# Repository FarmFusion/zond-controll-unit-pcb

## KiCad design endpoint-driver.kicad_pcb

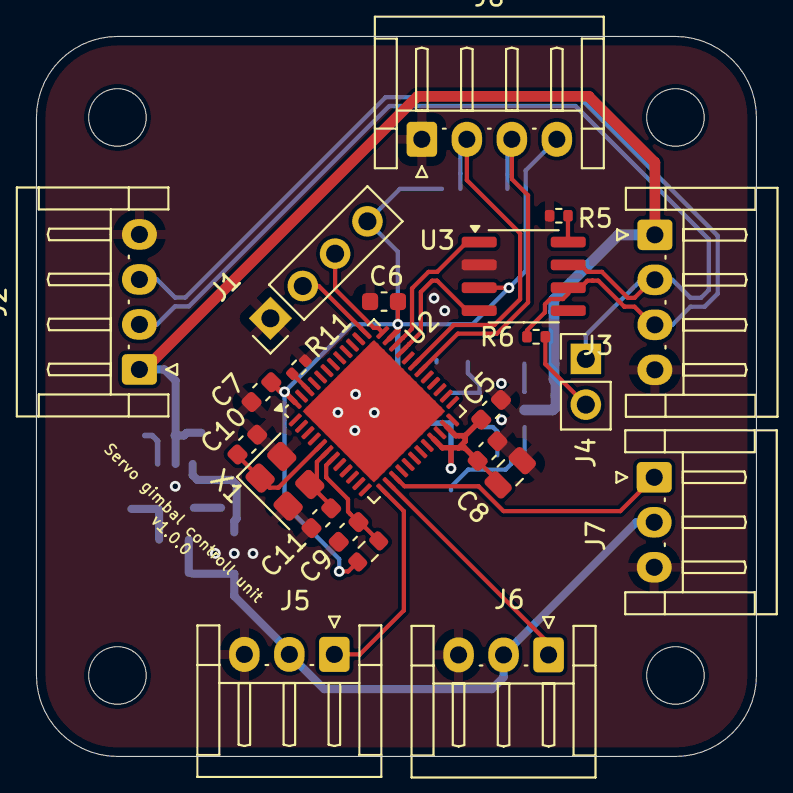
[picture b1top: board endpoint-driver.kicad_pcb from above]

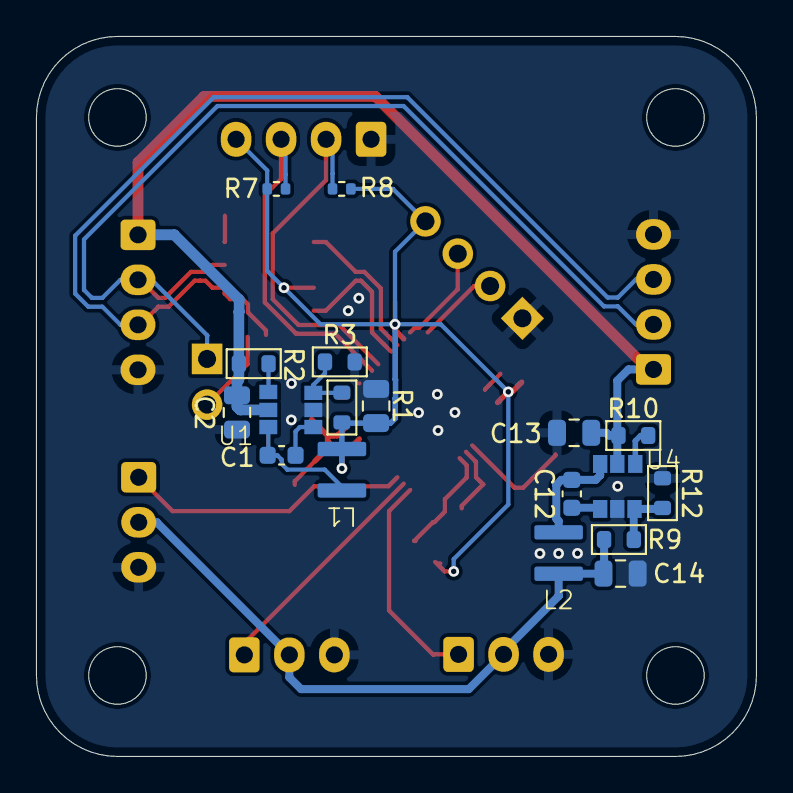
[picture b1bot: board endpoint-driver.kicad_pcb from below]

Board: 2 copper layers, 40.0 x 40.0 mm, 45 parts (18 on the bottom side), 29 nets.

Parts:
C1, C4, C5, C6, C7, C9, C12: 100nF; C_0603_1608Metric
C2, C13: 4.7uF; C_0805_2012Metric
C3, C8, C14: 10uF; C_0805_2012Metric
C10, C11: 20pF; C_0603_1608Metric
H1, H2, H3, H4: MountingHole_M3; MountingHole_3.2mm_M3
J1: Conn_01x04; PinHeader_1x04_P2.54mm_Vertical
J2, J3: Conn_01x04_Pin; JST_EH_S4B-EH_1x04_P2.50mm_Horizontal
J4: Conn_01x02_Pin; PinHeader_1x02_P2.54mm_Vertical
J5, J6, J7: Conn_01x03_Pin; JST_EH_S3B-EH_1x03_P2.50mm_Horizontal
J8: Conn_01x04; JST_EH_S4B-EH_1x04_P2.50mm_Horizontal
L1, L2: 4.7uH; SNR3015K-4R7M
R1, R9: 16kOm; R_0603_1608Metric
R2, R4, R10: 100kOm; R_0603_1608Metric
R3: 5.1kOm; R_0603_1608Metric
R5, R6, R7, R8, R11: 10kOm; R_0402_1005Metric
R12: 3kOm; R_0603_1608Metric
U1, U4: JW5017S
U2: STM32G431CBUx; QFN-48-1EP_7x7mm_P0.5mm_EP5.6x5.6mm
U3: SN65HVD230; SOIC-8_3.9x4.9mm_P1.27mm
X1: Crystal_Generic; Crystal_SMD_3225-4Pin_3.2x2.5mm

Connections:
+3.3V: C3.1, C4.1, C5.1, C6.1, C7.1, C8.1, J1.4, J8.4, L1.1, R1.1, R4.1, R7.1, R8.1, U2.21 (VDDA), U2.23 (VDD), U2.35 (VDD), U2.48 (VDD), U3.3 (VCC)
+5V: C14.1, J5.2, J6.2, J7.2, L2.1, R9.1
/CAN/CAN_N: J2.3, J3.3, R6.2, U3.6 (CANL)
/CAN/CAN_OUT+: U2.34 (PA12), U3.1 (D)
/CAN/CAN_OUT-: U2.33 (PA11), U3.4 (R)
/CAN/CAN_P: J2.2, J3.2, J4.1, U3.7 (CANH)
/MCU/BOOT: R11.1, U2.46 (PB8)
/MCU/EXTI_BTN1: J5.1, U2.13 (PA5)
/MCU/EXTI_BTN2: J6.1, U2.14 (PA6)
/MCU/EXTI_BTN3: J7.1, U2.15 (PA7)
/MCU/NRST: C9.1, R4.2, U2.7 (PG10)
/MCU/OSC_IN: C10.1, U2.5 (PF0), X1.1
/MCU/OSC_OUT: C11.2, U2.6 (PF1), X1.3
/MCU/SCL: J8.2, R8.2, U2.31 (PA9)
/MCU/SDA: J8.3, R7.2, U2.30 (PA8)
/MCU/SWCLK: J1.2, U2.37 (PA14)
/MCU/SWDIO: J1.3, U2.36 (PA13)
GND: C2.2, C3.2, C4.2, C5.2, C6.2, C7.2, C8.2, C9.2, C10.2, C11.1, C13.2, C14.2, J1.1, J2.4, J3.4, J5.3, J6.3, J7.3, J8.1, R3.2, R5.2, R11.2, R12.2, U1.2 (GND), U2.49 (VSS), U3.2 (GND), U4.2 (GND), X1.2, X1.4
unnamed: J4.2, R6.1
unnamed: C1.2, U1.1 (BST)
unnamed: R2.2, U1.4 (EN)
unnamed: R1.2, R3.1, U1.3 (FB)
unnamed: C1.1, L1.2, U1.6 (SW)
unnamed: R5.1, U3.8 (Rs)
unnamed: C12.2, U4.1 (BST)
unnamed: R10.2, U4.4 (EN)
unnamed: R9.2, R12.1, U4.3 (FB)
unnamed: C12.1, L2.2, U4.6 (SW)
VCC: C2.1, C13.1, J2.1, J3.1, R2.1, R10.1, U1.5 (VIN), U4.5 (VIN)

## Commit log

2025-05-21 Aprv
2025-05-31 Refactor PCB design parameters in endpoint-driver - Adjusted minimum hole-to-hole clearance from 0.25 to 0.24 in the .kicad_pro file for improved spacing.
